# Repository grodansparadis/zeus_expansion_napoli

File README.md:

<h1>Zeus Expansion Napoli</h1>

CAN add on card with Zeus expansion connector. Fits the 
<a href="http://www.grodansparadis.com/odessa/odessa.html">Odessa</a> module
among other modules.

<hr>

This project is part of the <a href="http://www.vscp.org">VSCP (Very Simple Control Protocol) project</a>. 

<hr>

This project is licensed under the 
<a href="http://creativecommons.org/licenses/by-nc-sa/3.0/">Creative Commons open source license Attribution-NonCommercial-ShareAlike 3.0 Unported</a>. 
Other license options are available by conacting <a href="malto:info@grodansparadis.com">Paradis of the Frog AB</a>

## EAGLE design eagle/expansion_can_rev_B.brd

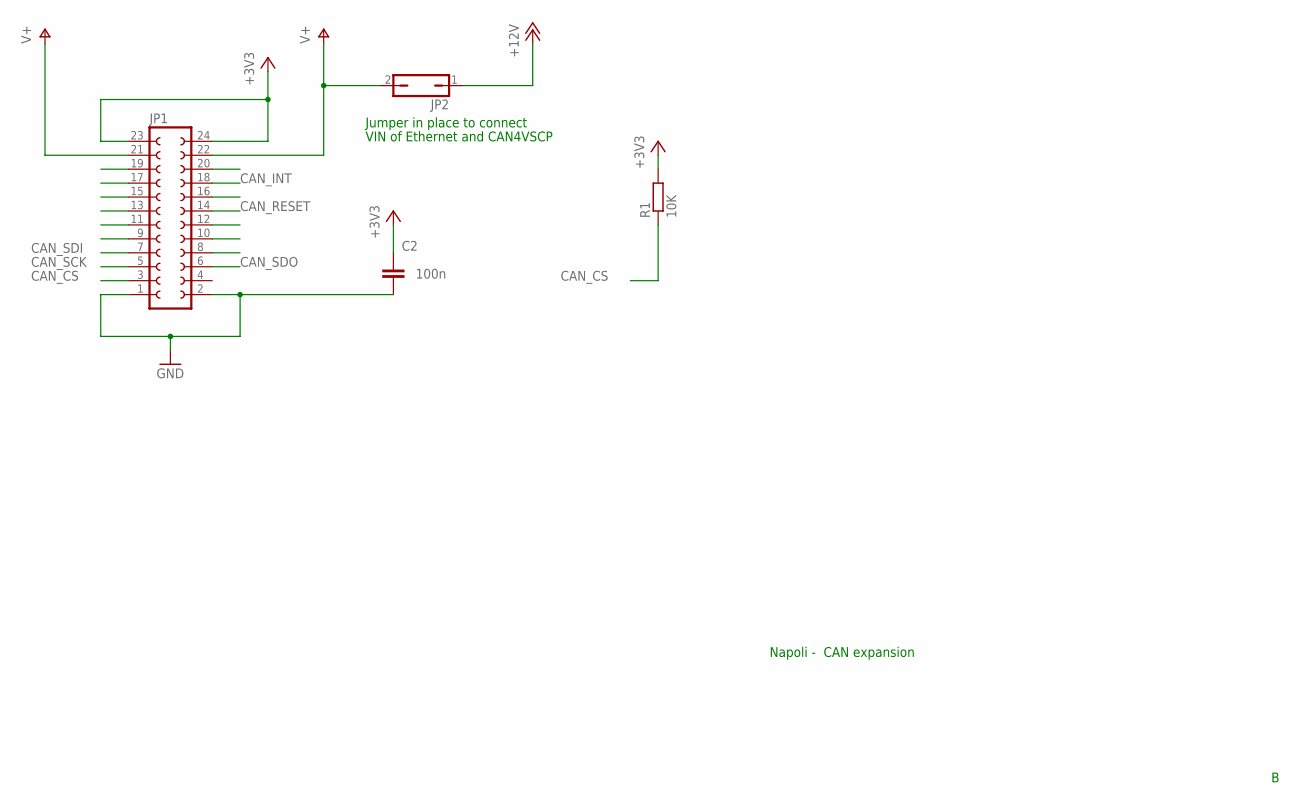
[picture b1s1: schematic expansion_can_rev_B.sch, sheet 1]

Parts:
C2: 100n; C0805
JP1: FE12-2
JP2: JP1Q; JP1
R1: 10K; R0805

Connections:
+3V3: C2.1, JP1.23, JP1.24, R1.2; also elsewhere on the board
+12V: JP2.1; also elsewhere on the board
CAN_CS: JP1.3, R1.1; also elsewhere on the board
CAN_INT: JP1.18; also elsewhere on the board
CAN_RESET: JP1.14; also elsewhere on the board
CAN_SCK: JP1.5; also elsewhere on the board
CAN_SDI: JP1.7; also elsewhere on the board
CAN_SDO: JP1.6; also elsewhere on the board
GND: C2.2, JP1.1, JP1.2; also elsewhere on the board
VIN: JP1.21, JP1.22, JP2.2

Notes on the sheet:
Napoli - CAN expansion
Jumper in place to connect
VIN of Ethernet and CAN4VSCP

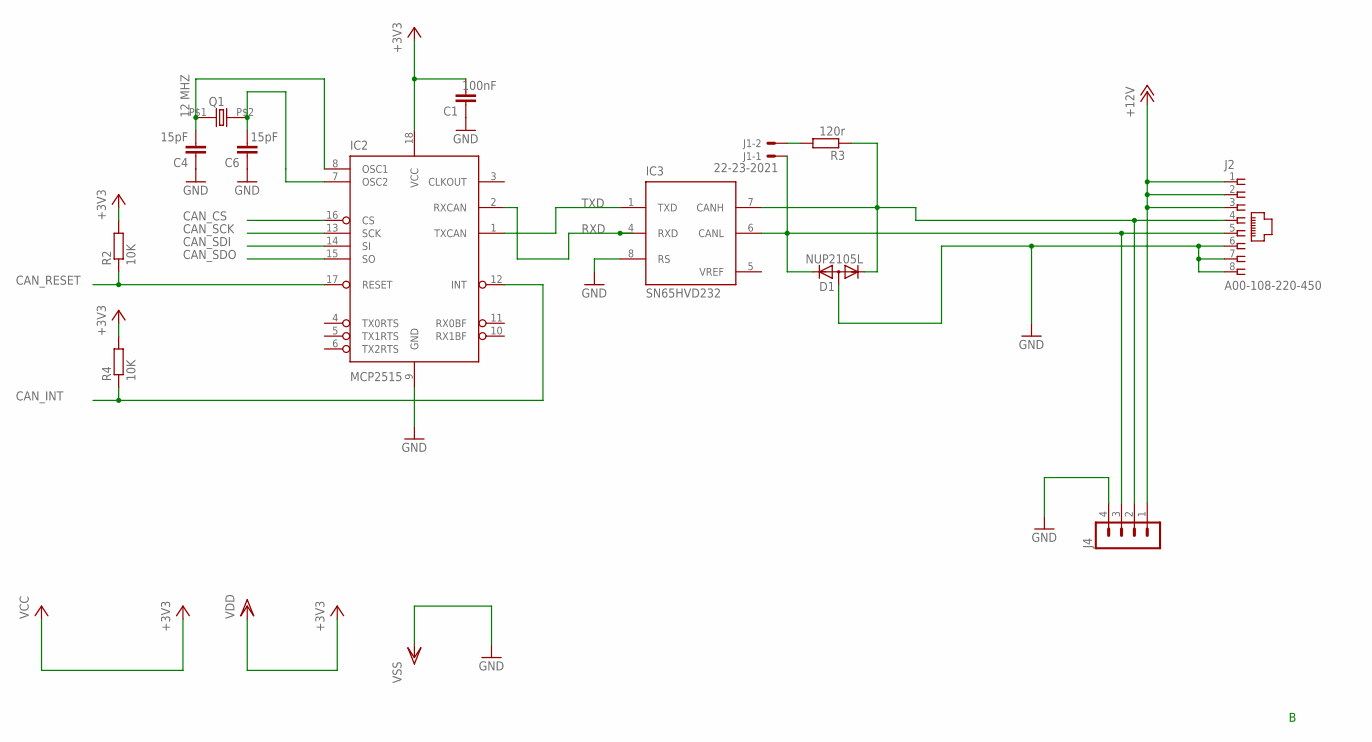
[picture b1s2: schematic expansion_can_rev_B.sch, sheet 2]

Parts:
C1: 100nF; C0805
C4, C6: 15pF; C0805
D1: NUP2105L; SOT23
IC2: MCP2515; SO-18W
IC3: SN65HVD232; SO-08
J1: 22-23-2021
J2: A00-108-220-450; RJ-45
J4: MA04-1
Q1: 12 MHZ; 9C
R2, R4: 10K; R0805
R3: 120r; R0805

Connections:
+3V3: C1.2, IC2.18 (VCC), IC3.3 (VDD), R2.2, R4.2; also elsewhere on the board
+12V: J2.1, J2.2, J2.3, J4.1; also elsewhere on the board
CANH: D1.1 (K1), IC3.7 (CANH), J2.4, J4.2, R3.1
CANL1: D1.2 (K2), IC3.6 (CANL), J1.1, J2.5, J4.3
CAN_CS: IC2.16 (CS); also elsewhere on the board
CAN_INT: IC2.12 (INT), R4.1; also elsewhere on the board
CAN_RESET: IC2.17 (RESET), R2.1; also elsewhere on the board
CAN_SCK: IC2.13 (SCK); also elsewhere on the board
CAN_SDI: IC2.14 (SI); also elsewhere on the board
CAN_SDO: IC2.15 (SO); also elsewhere on the board
GND: C1.1, C4.1, C6.1, D1.3 (A), IC2.9 (GND), IC3.2 (VSS), IC3.8 (RS), J2.6, J2.7, J2.8, J4.4; also elsewhere on the board
unnamed: J1.2, R3.2
unnamed: C4.2, IC2.8 (OSC1), Q1.P$1 (1)
unnamed: C6.2, IC2.7 (OSC2), Q1.P$2 (2)
RXD: IC2.2 (RXCAN), IC3.4 (RXD)
TXD: IC2.1 (TXCAN), IC3.1 (TXD)
VREF: IC3.5 (VREF)

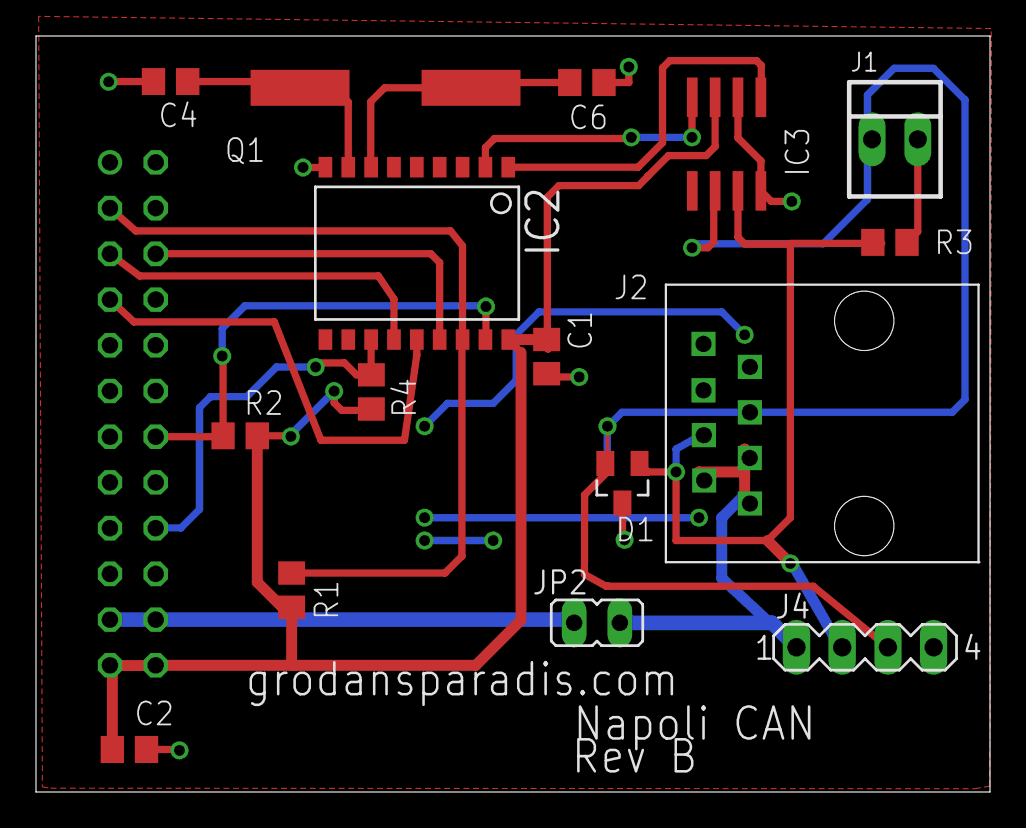
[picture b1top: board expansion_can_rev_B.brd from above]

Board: 2 copper layers, 53.0 x 42.0 mm, 17 parts (1 on the bottom side), 17 nets.

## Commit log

2015-11-03 Making design open
2015-11-03 Cleaned up some junk
2015-12-17 Updated readme and license
